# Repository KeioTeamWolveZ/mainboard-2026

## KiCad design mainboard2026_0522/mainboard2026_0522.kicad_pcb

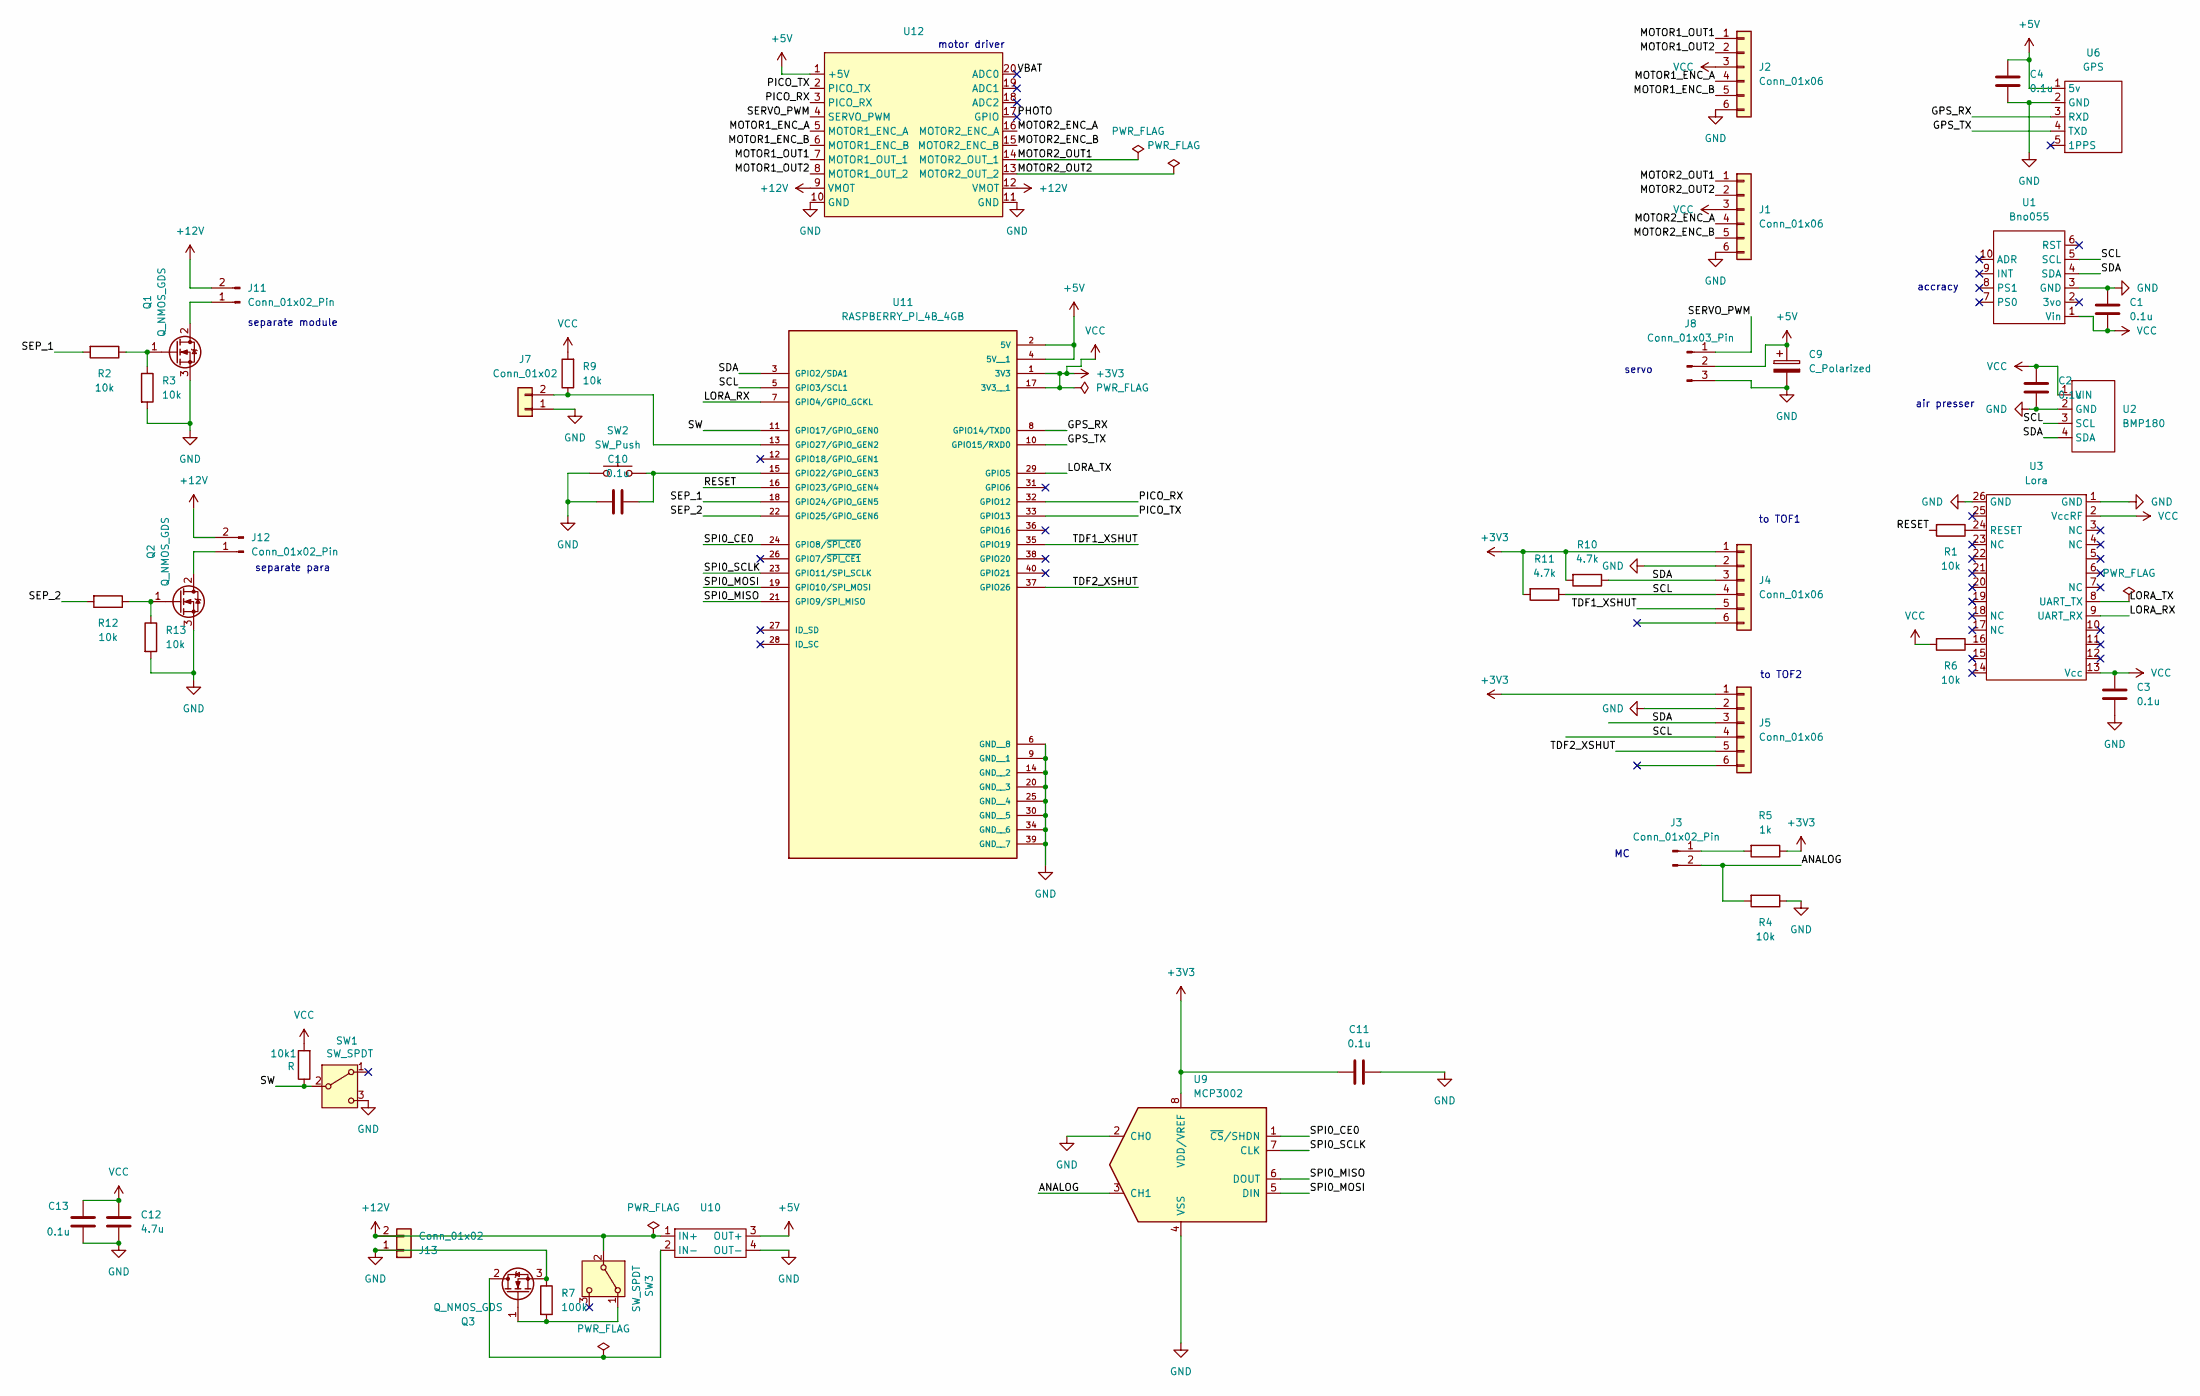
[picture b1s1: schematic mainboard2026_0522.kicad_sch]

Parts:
10k1: R; R_0603_1608Metric_Pad0.98x0.95mm_HandSolder
C1, C2, C3, C4, C10, C11, C13: 0.1u; C_0603_1608Metric_Pad1.08x0.95mm_HandSolder
C9: C_Polarized; CP_Radial_D6.3mm_P2.50mm
C12: 4.7u; C_0603_1608Metric_Pad1.08x0.95mm_HandSolder
J1, J2: Conn_01x06; JST_XH_S6B-XH-A-1_1x06_P2.50mm_Horizontal
J3, J11, J12: Conn_01x02_Pin; JST_PH_B2B-PH-K_1x02_P2.00mm_Vertical
J4, J5: Conn_01x06; JST_ZH_B6B-ZR_1x06_P1.50mm_Horizontal
J7: Conn_01x02; PinHeader_1x02_P2.54mm_Vertical
J8: Conn_01x03_Pin; JST_PH_B3B-PH-K_1x03_P2.00mm_Vertical
J13: Conn_01x02; AMASS_XT30U-M_1x02_P5.0mm_Vertical
Q1, Q2, Q3: Q_NMOS_GDS; TO-252-3_TabPin2
R1, R2, R3, R6, R9, R12, R13: 10k; R_0603_1608Metric_Pad0.98x0.95mm_HandSolder
R4: 10k; R_Axial_DIN0207_L6.3mm_D2.5mm_P10.16mm_Horizontal
R5: 1k; R_Axial_DIN0207_L6.3mm_D2.5mm_P10.16mm_Horizontal
R7: 100k; R_0603_1608Metric_Pad0.98x0.95mm_HandSolder
R10, R11: 4.7k; R_0603_1608Metric_Pad0.98x0.95mm_HandSolder
SW1, SW3: SW_SPDT; SW_Slide-03_Wuerth-WS-SLTV_10x2.5x6.4_P2.54mm
SW2: SW_Push; SW_PUSH_6mm_H7.3mm
U1: Bno055
U2: BMP180; PinHeader_1x04_P2.54mm_Vertical
U3: Lora; LoRa
U6: GPS
U9: MCP3002; DIP-8_W7.62mm
U10: OKL
U11: RASPBERRY_PI_4B_4GB; raspberrypi; PARTREV 4
U12: motor

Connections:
+3V3: 10k1.2, C1.2, C2.1, C3.1, C11.1, C12.2, C13.2, J1.3, J2.3, J4.1, J5.1, R5.1, R6.2, R9.2, R10.2, R11.2, U1.1 (Vin), U2.1 (VIN), U3.2 (VccRF), U3.13 (Vcc), U9.8 (VDD/VREF), U11.1 (3V3), U11.17 (3V3__1)
+5V: C4.1, C9.1, J8.2, U6.1 (5v~), U10.3 (OUT+), U11.2 (5V), U11.4 (5V__1), U12.1 (+5V)
+12V: J11.2, J12.2, J13.2, SW3.2 (B), U10.1 (IN+), U12.9 (VMOT), U12.12 (VMOT)
/ANALOG: J3.2, R4.2, U9.3 (CH1)
/GPS_RX: U6.3 (RXD~), U11.8 (GPIO14/TXD0)
/GPS_TX: U6.4 (TXD~), U11.10 (GPIO15/RXD0)
/LORA_RX: U3.9 (UART_RX), U11.7 (GPIO4/GPIO_GCKL)
/LORA_TX: U3.8 (UART_TX), U11.29 (GPIO5)
/MOTOR1_ENC_A: J2.4, U12.5 (MOTOR1_ENC_A)
/MOTOR1_ENC_B: J2.5, U12.6 (MOTOR1_ENC_B)
/MOTOR1_OUT1: J2.1, U12.7 (MOTOR1_OUT_1)
/MOTOR1_OUT2: J2.2, U12.8 (MOTOR1_OUT_2)
/MOTOR2_ENC_A: J1.4, U12.16 (MOTOR2_ENC_A)
/MOTOR2_ENC_B: J1.5, U12.15 (MOTOR2_ENC_B)
/MOTOR2_OUT1: J1.1, U12.14 (MOTOR2_OUT_1)
/MOTOR2_OUT2: J1.2, U12.13 (MOTOR2_OUT_2)
/PHOTO: U12.17 (GPIO)
/PICO_RX: U11.32 (GPIO12), U12.3 (PICO_RX)
/PICO_TX: U11.33 (GPIO13), U12.2 (PICO_TX)
/RESET: R1.2, U11.16 (GPIO23/GPIO_GEN4)
/SCL: J4.4, J5.4, R11.1, U1.5 (SCL), U2.3 (SCL), U11.5 (GPIO3/SCL1)
/SDA: J4.3, J5.3, R10.1, U1.4 (SDA), U2.4 (SDA), U11.3 (GPIO2/SDA1)
/SEP_1: R2.2, U11.18 (GPIO24/GPIO_GEN5)
/SEP_2: R12.2, U11.22 (GPIO25/GPIO_GEN6)
/SERVO_PWM: J8.1, U12.4 (SERVO_PWM)
/SPI0_CE0: U9.1 (~CS/SHDN), U11.24 (GPIO8/~SPI_CE0)
/SPI0_MISO: U9.6 (DOUT), U11.21 (GPIO9/SPI_MISO)
/SPI0_MOSI: U9.5 (DIN), U11.19 (GPIO10/SPI_MOSI)
/SPI0_SCLK: U9.7 (CLK), U11.23 (GPIO11/SPI_SCLK)
/SW: 10k1.1, SW1.2 (B), U11.11 (GPIO17/GPIO_GEN0)
/TDF1_XSHUT: J4.5, U11.35 (GPIO19)
/TDF2_XSHUT: J5.5, U11.37 (GPIO26)
/VBAT: U12.20 (ADC0)
GND: C1.1, C2.2, C3.2, C4.2, C9.2, C10.1, C11.2, C12.1, C13.1, J1.6, J2.6, J4.2, J5.2, J7.1, J8.3, J13.1, Q1.3 (S), Q2.3 (S), Q3.3 (S), R3.2, R4.1, R7.1, R13.2, SW1.3 (C), SW2.1, U1.3 (GND), U2.2 (GND), U3.1 (GND), U3.26 (GND), U6.2 (GND~), U9.2 (CH0), U9.4 (VSS), U10.4 (OUT-), U11.6 (GND__8), U11.9 (GND__1), U11.14 (GND__2), U11.20 (GND__3), U11.25 (GND__4), U11.30 (GND__5), U11.34 (GND__6), U11.39 (GND__7), U12.10 (GND), U12.11 (GND)
unnamed: J3.1, R5.2
unnamed: J7.2, R9.1, U11.13 (GPIO27/GPIO_GEN2)
unnamed: J11.1, Q1.2 (D)
unnamed: J12.1, Q2.2 (D)
unnamed: Q1.1 (G), R2.1, R3.1
unnamed: Q2.1 (G), R12.1, R13.1
unnamed: Q3.2 (D), U10.2 (IN-)
unnamed: Q3.1 (G), R7.2, SW3.1 (A)
unnamed: R6.1, U3.16
unnamed: R1.1, U3.24 (RESET)
unnamed: C10.2, SW2.2, U11.15 (GPIO22/GPIO_GEN3)

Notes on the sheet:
accracy
air presser
separate para
to TOF1
motor driver
to TOF2
separate module
servo

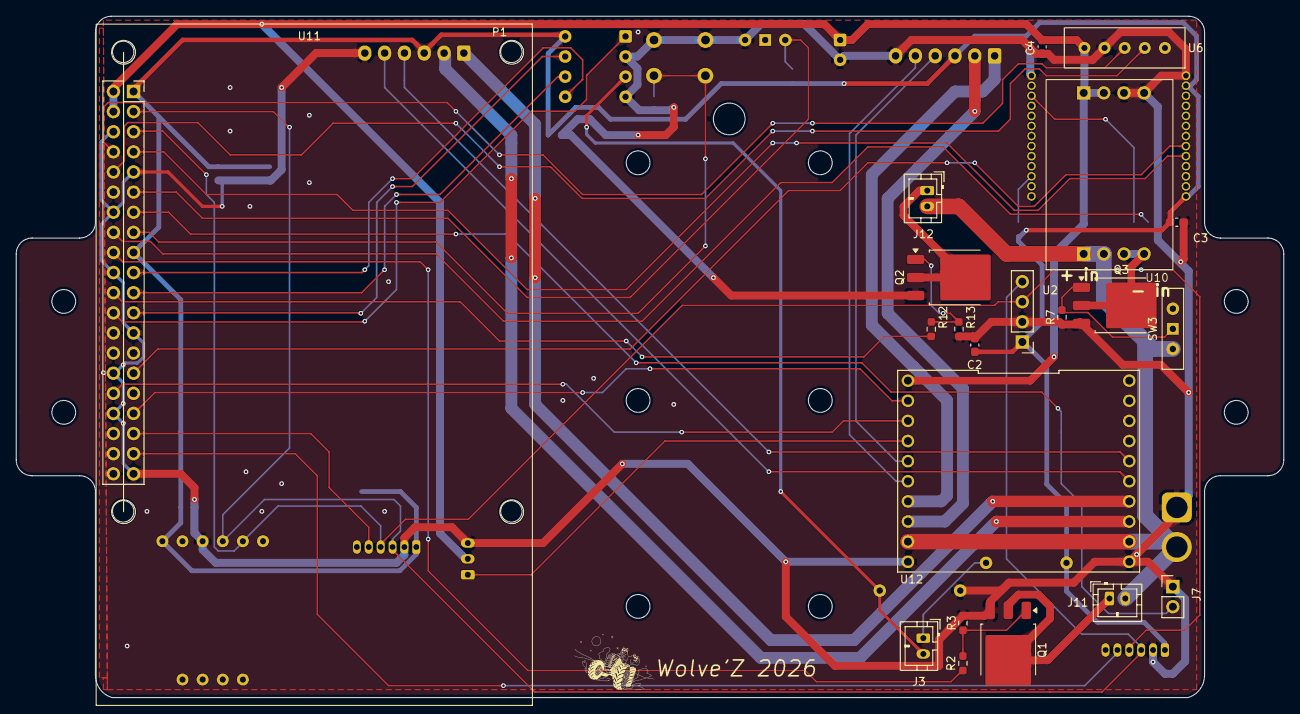
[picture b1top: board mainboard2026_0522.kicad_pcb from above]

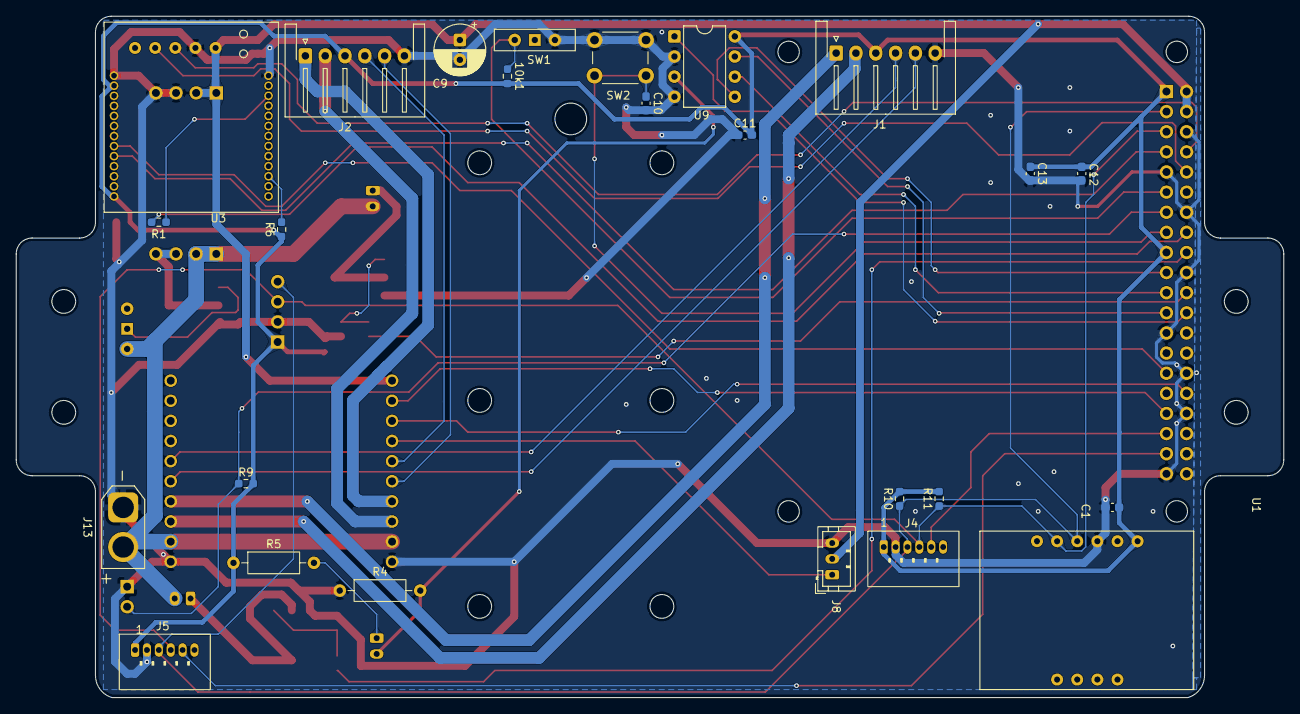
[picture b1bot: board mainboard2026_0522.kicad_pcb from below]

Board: 2 copper layers, 160.0 x 86.0 mm, 46 parts (25 on the bottom side), 43 nets.

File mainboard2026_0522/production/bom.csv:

Designator,Footprint,Quantity,Value,LCSC Part #
10K1,0603,1,R,
"C1, C10, C11, C13, C2, C3, C4",0603,7,0.1u,
C12,0603,1,4.7u,
C9,CP_Radial_D6.3mm_P2.50mm,1,C_Polarized,
"J1, J2",JST_XH_S6B-XH-A-1_1x06_P2.50mm_Horizontal,2,Conn_01x06,
"J11, J12, J3",JST_PH_B2B-PH-K_1x02_P2.00mm_Vertical,3,Conn_01x02_Pin,
J13,AMASS_XT30U-M_1x02_P5.0mm_Vertical,1,Conn_01x02,
"J4, J5",JST_ZH_B6B-ZR_1x06_P1.50mm_Horizontal,2,Conn_01x06,
J7,PinHeader_1x02_P2.54mm_Vertical,1,Conn_01x02,
J8,JST_PH_B3B-PH-K_1x03_P2.00mm_Vertical,1,Conn_01x03_Pin,
"Q1, Q2",TO-252-3_TabPin2,2,Q_NMOS_GDS,
"R1, R12, R13, R2, R3, R4, R6, R9",0603,8,10k,
"R10, R11",0603,2,4.7k,
R5,0603,1,1k,
SW1,SW_Slide-03_Wuerth-WS-SLTV_10x2.5x6.4_P2.54mm,1,SW_SPDT,
SW2,SW_PUSH_6mm_H7.3mm,1,SW_Push,
U1,Bno055,1,Bno055,
U10,OKL,1,~,
U11,raspberrypi,1,RASPBERRY_PI_4B_4GB,
U12,motor,1,~,
U2,PinHeader_1x04_P2.54mm_Vertical,1,BMP180,
U3,LoRa,1,Lora,
U6,GPS,1,GPS,
U9,DIP-8_W7.62mm,1,MCP3002,

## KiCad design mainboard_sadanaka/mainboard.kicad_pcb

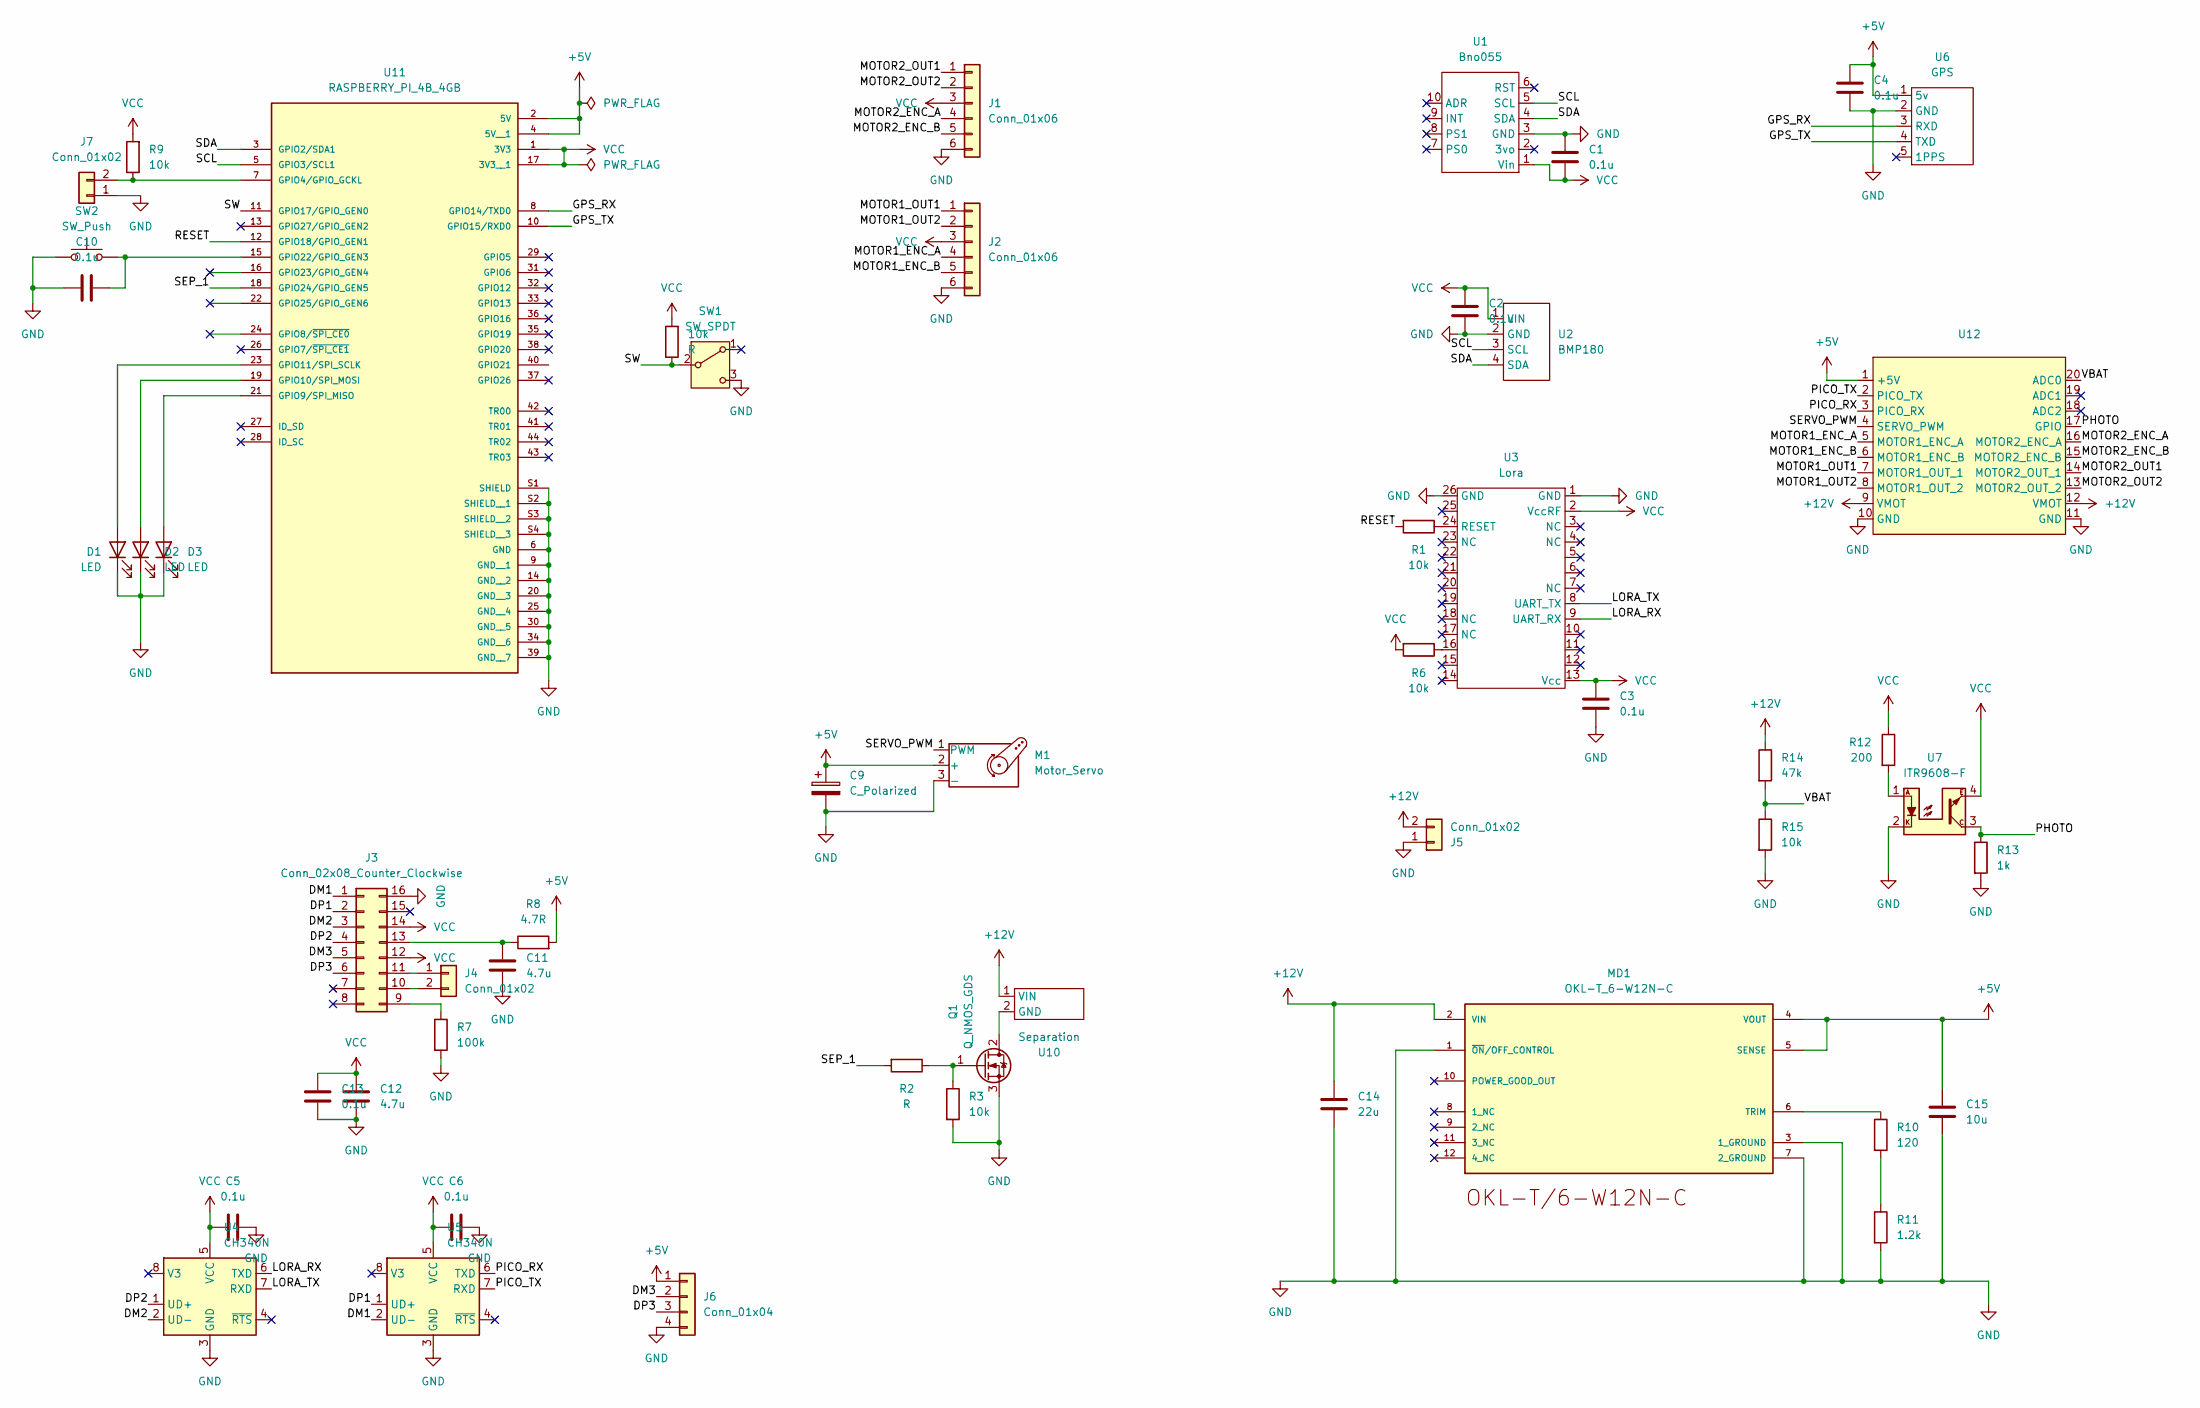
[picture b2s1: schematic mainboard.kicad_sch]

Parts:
10k: R; R_0603_1608Metric_Pad0.98x0.95mm_HandSolder
C1, C2, C3, C4, C5, C6, C10, C13: 0.1u; C_0603_1608Metric_Pad1.08x0.95mm_HandSolder
C9: C_Polarized; CP_Radial_D6.3mm_P2.50mm
C11, C12: 4.7u; C_0603_1608Metric_Pad1.08x0.95mm_HandSolder
C14: 22u; C_0805_2012Metric_Pad1.18x1.45mm_HandSolder
C15: 10u; C_0603_1608Metric_Pad1.08x0.95mm_HandSolder
D1, D2, D3: LED; LED_D3.0mm
J1, J2: Conn_01x06; JST_XH_S6B-XH-A-1_1x06_P2.50mm_Horizontal
J3: Conn_02x08_Counter_Clockwise; SOP-16_4.4x10.4mm_P1.27mm
J4: Conn_01x02; JST_PH_B2B-PH-K_1x02_P2.00mm_Vertical
J5: Conn_01x02; AMASS_XT30U-M_1x02_P5.0mm_Vertical
J6: Conn_01x04; PinHeader_1x04_P2.54mm_Horizontal
J7: Conn_01x02; PinHeader_1x02_P2.54mm_Vertical
M1: Motor_Servo; JST_XH_B3B-XH-A_1x03_P2.50mm_Vertical
MD1: OKL-T_6-W12N-C; MURATA_OKL-T-6-W12N-C_0; MOUSER_PART_NUMBER 580-OKL-T/6-W12N-C; MOUSER_DESCRIPTION Non-Isolated DC/DC Converters 12Vin .59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
Q1: Q_NMOS_GDS; TO-252-3_TabPin2
R1, R3, R6, R9, R15: 10k; R_0603_1608Metric_Pad0.98x0.95mm_HandSolder
R2: R; R_0603_1608Metric_Pad0.98x0.95mm_HandSolder
R7: 100k; R_0603_1608Metric_Pad0.98x0.95mm_HandSolder
R8: 4.7R; R_0603_1608Metric_Pad0.98x0.95mm_HandSolder
R10: 120; R_0603_1608Metric_Pad0.98x0.95mm_HandSolder
R11: 1.2k; R_0603_1608Metric_Pad0.98x0.95mm_HandSolder
R12: 200; R_0603_1608Metric_Pad0.98x0.95mm_HandSolder
R13: 1k; R_0603_1608Metric_Pad0.98x0.95mm_HandSolder
R14: 47k; R_0603_1608Metric_Pad0.98x0.95mm_HandSolder
SW1: SW_SPDT; SW_Slide-03_Wuerth-WS-SLTV_10x2.5x6.4_P2.54mm
SW2: SW_Push; SW_PUSH_6mm_H7.3mm
U1: Bno055
U2: BMP180; PinHeader_1x04_P2.54mm_Vertical
U3: Lora; LoRa
U4, U5: CH340N; SOP-8_3.9x4.9mm_P1.27mm
U6: GPS
U7: ITR9608-F; PinHeader_2x02_P2.54mm_Vertical
U10: Separation; JST_XH_S2B-XH-A_1x02_P2.50mm_Horizontal
U11: RASPBERRY_PI_4B_4GB; Raspberry_Pi_Zero_Socketed_THT_FaceDown_MountingHoles; PARTREV 4
U12: motor

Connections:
+5V: C4.1, C9.1, C15.1, J6.1, M1.2 (+), MD1.4 (VOUT), MD1.5 (SENSE), R8.2, U6.1 (5v~), U11.2 (5V), U11.4 (5V__1), U12.1 (+5V)
+12V: C14.1, J5.2, MD1.2 (VIN), R14.1, U10.1 (VIN), U12.9 (VMOT), U12.12 (VMOT)
/DM1: J3.1, U5.2 (UD-)
/DM2: J3.3, U4.2 (UD-)
/DM3: J3.5, J6.2
/DP1: J3.2, U5.1 (UD+)
/DP2: J3.4, U4.1 (UD+)
/DP3: J3.6, J6.3
/GPS_RX: U6.3 (RXD~), U11.8 (GPIO14/TXD0)
/GPS_TX: U6.4 (TXD~), U11.10 (GPIO15/RXD0)
/LORA_RX: U3.9 (UART_RX), U4.6 (TXD)
/LORA_TX: U3.8 (UART_TX), U4.7 (RXD)
/MOTOR1_ENC_A: J2.4, U12.5 (MOTOR1_ENC_A)
/MOTOR1_ENC_B: J2.5, U12.6 (MOTOR1_ENC_B)
/MOTOR1_OUT1: J2.1, U12.7 (MOTOR1_OUT_1)
/MOTOR1_OUT2: J2.2, U12.8 (MOTOR1_OUT_2)
/MOTOR2_ENC_A: J1.4, U12.16 (MOTOR2_ENC_A)
/MOTOR2_ENC_B: J1.5, U12.15 (MOTOR2_ENC_B)
/MOTOR2_OUT1: J1.1, U12.14 (MOTOR2_OUT_1)
/MOTOR2_OUT2: J1.2, U12.13 (MOTOR2_OUT_2)
/PHOTO: R13.1, U7.3, U12.17 (GPIO)
/PICO_RX: U5.6 (TXD), U12.3 (PICO_RX)
/PICO_TX: U5.7 (RXD), U12.2 (PICO_TX)
/RESET: R1.2, U11.12 (GPIO18/GPIO_GEN1)
/SCL: U1.5 (SCL), U2.3 (SCL), U11.5 (GPIO3/SCL1)
/SDA: U1.4 (SDA), U2.4 (SDA), U11.3 (GPIO2/SDA1)
/SEP_1: R2.2, U11.18 (GPIO24/GPIO_GEN5)
/SERVO_PWM: M1.1 (PWM), U12.4 (SERVO_PWM)
/SW: 10k.1, SW1.2 (B), U11.11 (GPIO17/GPIO_GEN0); also elsewhere on the board
/VBAT: R14.2, R15.1, U12.20 (ADC0)
GND: C1.1, C2.2, C3.2, C4.2, C5.1, C6.1, C9.2, C10.1, C11.1, C12.1, C13.1, C14.2, C15.2, D1.1 (K), D2.1 (K), D3.1 (K), J1.6, J2.6, J3.16, J5.1, J6.4, J7.1, M1.3 (-), MD1.1 (~ON/OFF_CONTROL), MD1.3 (1_GROUND), MD1.7 (2_GROUND), Q1.3 (S), R3.2, R7.2, R11.2, R13.2, R15.2, SW1.3 (C), SW2.1, U1.3 (GND), U2.2 (GND), U3.1 (GND), U3.26 (GND), U4.3 (GND), U5.3 (GND), U6.2 (GND~), U7.2, U11.6 (GND), U11.9 (GND__1), U11.14 (GND__2), U11.20 (GND__3), U11.25 (GND__4), U11.30 (GND__5), U11.34 (GND__6), U11.39 (GND__7), U11.S1 (SHIELD), U11.S2 (SHIELD__1), U11.S3 (SHIELD__2), U11.S4 (SHIELD__3), U12.10 (GND), U12.11 (GND)
unnamed: D1.2 (A), U11.23 (GPIO11/SPI_SCLK)
unnamed: D2.2 (A), U11.19 (GPIO10/SPI_MOSI)
unnamed: D3.2 (A), U11.21 (GPIO9/SPI_MISO)
unnamed: J3.9, R7.1
unnamed: J3.10, J4.2
unnamed: J3.11, J4.1
unnamed: C11.2, J3.13, R8.1
unnamed: J7.2, R9.1, U11.7 (GPIO4/GPIO_GCKL)
unnamed: MD1.6 (TRIM), R10.1
unnamed: Q1.2 (D), U10.2 (GND)
unnamed: Q1.1 (G), R2.1, R3.1
unnamed: R6.1, U3.16
unnamed: R10.2, R11.1
unnamed: R12.2, U7.1
unnamed: R1.1, U3.24 (RESET)
unnamed: C10.2, SW2.2, U11.15 (GPIO22/GPIO_GEN3)
VCC: 10k.2, C1.2, C2.1, C3.1, C5.2, C6.2, C12.2, C13.2, J1.3, J2.3, J3.12, J3.14, R6.2, R9.2, R12.1, U1.1 (Vin), U2.1 (VIN), U3.2 (VccRF), U3.13 (Vcc), U4.5 (VCC), U5.5 (VCC), U7.4, U11.1 (3V3), U11.17 (3V3__1); also elsewhere on the board

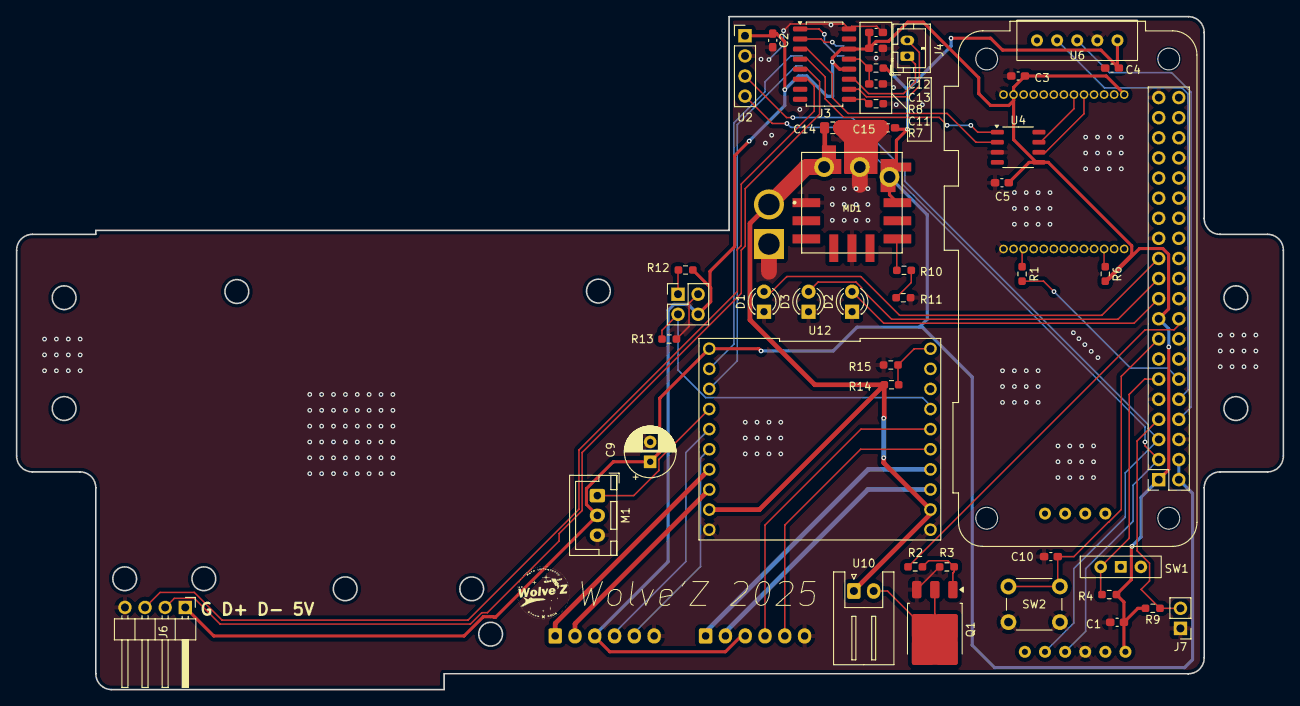
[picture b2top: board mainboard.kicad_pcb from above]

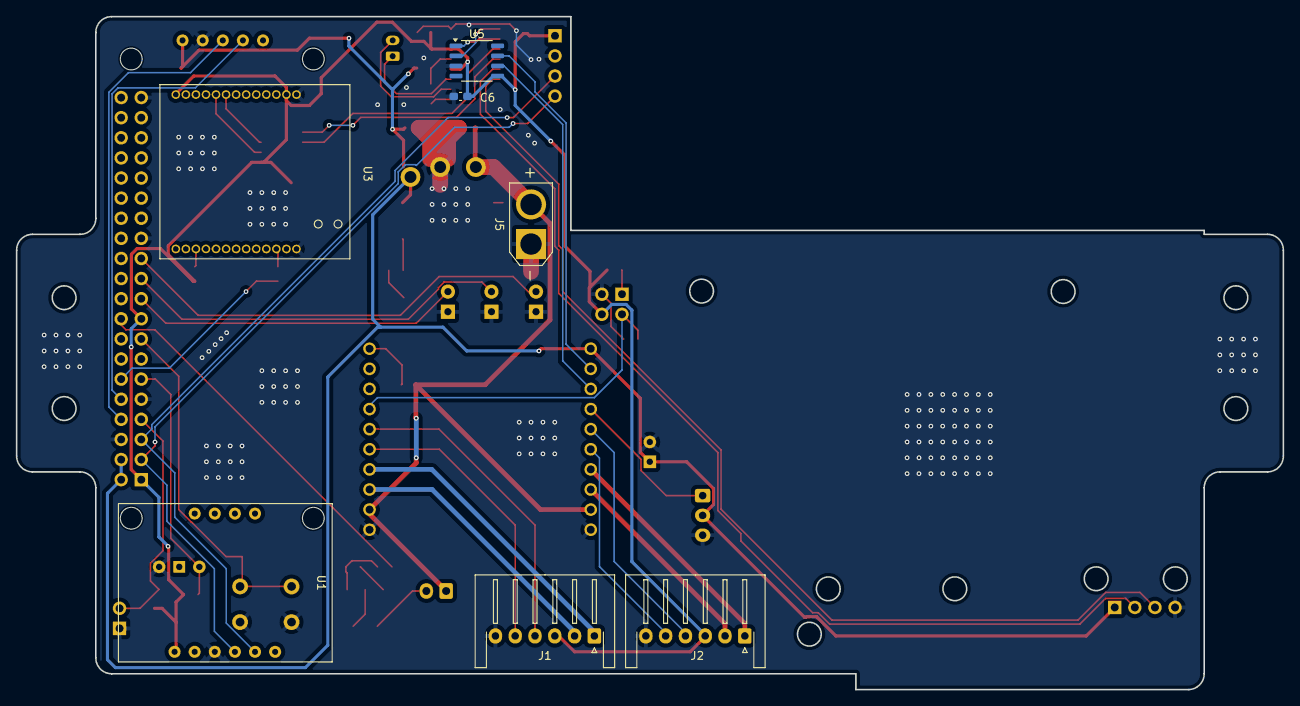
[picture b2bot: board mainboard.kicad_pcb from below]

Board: 2 copper layers, 160.0 x 85.0 mm, 52 parts (7 on the bottom side), 48 nets.

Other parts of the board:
R4: R; R_0603_1608Metric_Pad0.98x0.95mm_HandSolder

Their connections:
/SW: R4.1; also elsewhere on the board
VCC: R4.2; also elsewhere on the board

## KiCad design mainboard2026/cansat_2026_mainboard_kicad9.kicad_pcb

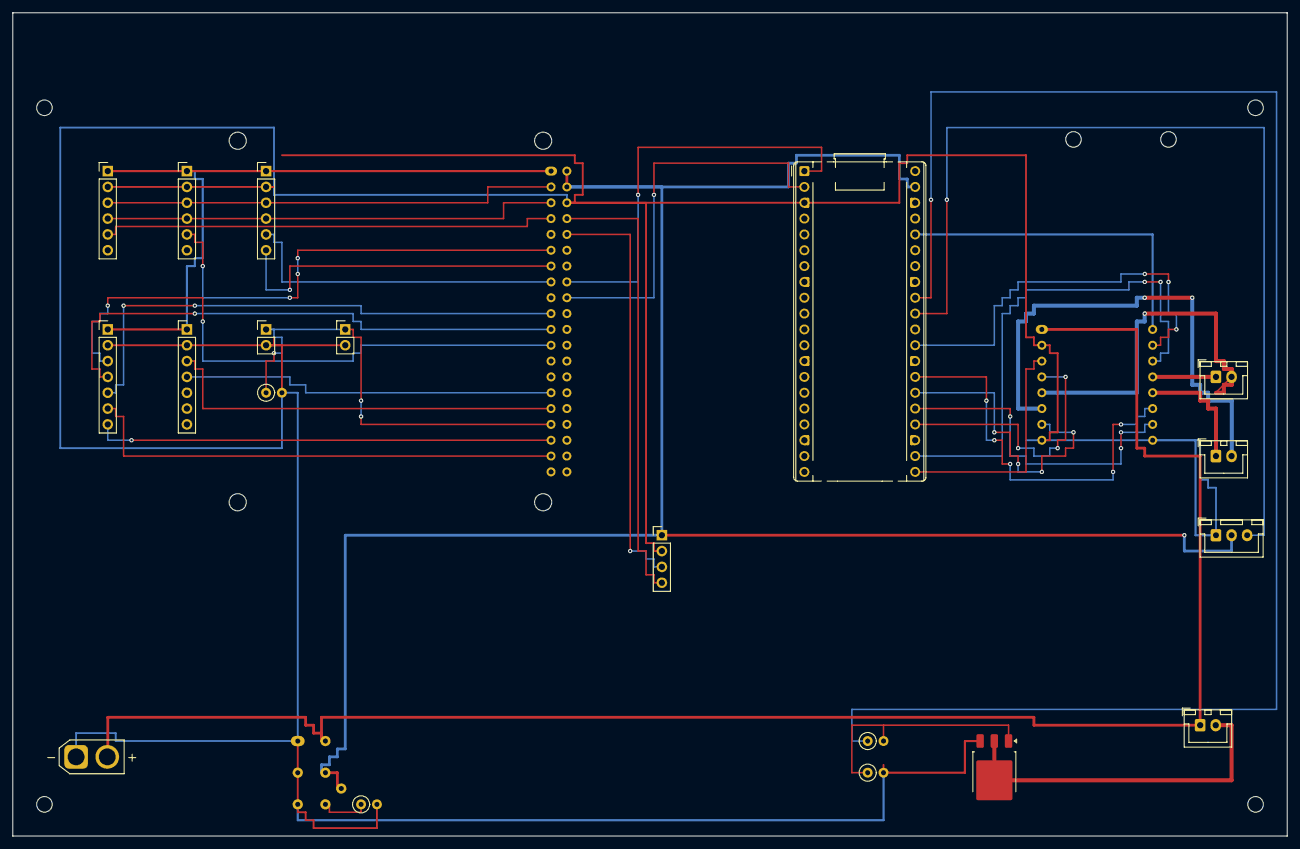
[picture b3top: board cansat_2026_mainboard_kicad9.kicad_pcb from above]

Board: 2 copper layers, 204.5 x 132.1 mm, 28 parts (0 on the bottom side), 39 nets.

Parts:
J_GPS1: u-blox NEO-M8N UART GPS module; PinHeader_1x04_P2.54mm_Vertical
J_IMU1: Adafruit 4754 BNO085 9-DoF IMU; PinHeader_1x06_P2.54mm_Vertical
J_LORA1: Ebyte E220-900T22S LoRa UART; PinHeader_1x07_P2.54mm_Vertical
J_MAG_MOD: 2-pin magnetic connector module; PinHeader_1x02_P2.54mm_Vertical
J_MAG_STAB: 2-pin magnetic connector stabilizer; PinHeader_1x02_P2.54mm_Vertical
J_MOTDRV1: SparkFun ROB-14451 TB6612FNG dual motor driver; SparkFun_TB6612FNG_Carrier_2x08_17.78mm
J_MOTOR_A: JST-XH B2B-XH-A Motor A; JST_XH_B2B-XH-A_1x02_P2.50mm_Vertical
J_MOTOR_B: JST-XH B2B-XH-A Motor B; JST_XH_B2B-XH-A_1x02_P2.50mm_Vertical
J_PWR1: AMASS XT30U-M 12V input; AMASS_XT30U-M_1x02_P5.0mm_Vertical
J_RPI1: Raspberry Pi 4 Model B full-envelope 40-pin inter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; RaspberryPi_4B_40pin_Mount
J_SD1: Adafruit 4682 microSD SPI breakout; PinHeader_1x07_P2.54mm_Vertical
J_SEP1: JST-XH B2B-XH-A separation nichrome; JST_XH_B2B-XH-A_1x02_P2.50mm_Vertical
J_SERVO1: JST-XH B3B-XH-A servo; JST_XH_B3B-XH-A_1x03_P2.50mm_Vertical
J_TOF1: Adafruit 3967 VL53L1X ToF front; PinHeader_1x06_P2.54mm_Vertical
J_TOF2: Adafruit 3967 VL53L1X ToF rear; PinHeader_1x06_P2.54mm_Vertical
MD1: Murata OKL-T/6-W12N-C 12V-to-5V; Murata_OKL-T-6-W12N-C
MH1, MH2, MH3, MH4: M2.5 mounting hole; MountingHole_2.5mm
MH_CAM1, MH_CAM2: Camera cable strain relief M2.5; MountingHole_2.5mm
Q1: IRLR7843PbF NMOS separation low-side; TO-252-3_TabPin2
R_MAG: 10k magnetic detect pulldown; R_Axial_DIN0207_L6.3mm_D2.5mm_P2.54mm_Vertical
R_SEP_G: 100R gate resistor; R_Axial_DIN0207_L6.3mm_D2.5mm_P2.54mm_Vertical
R_SEP_PD: 100k gate pulldown; R_Axial_DIN0207_L6.3mm_D2.5mm_P2.54mm_Vertical
R_TRIM1: DNP OKL trim placeholder; R_Axial_DIN0207_L6.3mm_D2.5mm_P2.54mm_Vertical
U_PICO1: Raspberry Pi Pico H SC0917 motor MCU; RaspberryPi_Pico_Common_THT

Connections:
+3V3: J_IMU1.1, J_LORA1.1, J_RPI1.1, J_SD1.1, J_TOF1.1, J_TOF2.1
+5V: J_GPS1.1, J_RPI1.2, J_RPI1.4, J_SERVO1.2, MD1.4, MD1.5, U_PICO1.39
+12V: J_MOTDRV1.1, J_PWR1.2, J_SEP1.1, MD1.2
BNO_INT: J_IMU1.5, J_RPI1.15
BNO_RST: J_IMU1.6, J_RPI1.13
GND: J_GPS1.2, J_IMU1.2, J_LORA1.2, J_MAG_MOD.2, J_MAG_STAB.2, J_MOTDRV1.3, J_MOTDRV1.15, J_MOTDRV1.16, J_PWR1.1, J_RPI1.6, J_SD1.2, J_SERVO1.1, J_TOF1.2, J_TOF2.2, MD1.1, MD1.3, MD1.7, Q1.3, R_MAG.2, R_SEP_PD.2, R_TRIM1.2, U_PICO1.3
GPS_RX_FROM_PI: J_GPS1.4, J_RPI1.8
GPS_TX_TO_PI: J_GPS1.3, J_RPI1.10
I2C_SCL: J_IMU1.4, J_RPI1.5, J_TOF1.4, J_TOF2.4
I2C_SDA: J_IMU1.3, J_RPI1.3, J_TOF1.3, J_TOF2.3
LORA_RXD_FROM_PI: J_LORA1.4, J_RPI1.29
LORA_TXD_TO_PI: J_LORA1.3, J_RPI1.31
MAG_DETECT: J_MAG_MOD.1, J_MAG_STAB.1, J_RPI1.33, R_MAG.1
MD1_TRIM: MD1.6, R_TRIM1.1
MOTOR_A1: J_MOTDRV1.8, J_MOTOR_A.1
MOTOR_A2: J_MOTDRV1.9, J_MOTOR_A.2
MOTOR_B1: J_MOTDRV1.10, J_MOTOR_B.1
MOTOR_B2: J_MOTDRV1.11, J_MOTOR_B.2
MOT_AIN1: J_MOTDRV1.5, U_PICO1.21
MOT_AIN2: J_MOTDRV1.6, U_PICO1.22
MOT_BIN1: J_MOTDRV1.14, U_PICO1.25
MOT_BIN2: J_MOTDRV1.13, U_PICO1.26
MOT_PWMA: J_MOTDRV1.7, U_PICO1.24
MOT_PWMB: J_MOTDRV1.12, U_PICO1.27
MOT_STBY: J_MOTDRV1.4, U_PICO1.29
PICO_3V3: J_MOTDRV1.2, U_PICO1.36
PICO_TO_PI: J_RPI1.18, U_PICO1.2
PI_TO_PICO: J_RPI1.16, U_PICO1.1
SD_CS: J_RPI1.37, J_SD1.6
SD_DET: J_RPI1.35, J_SD1.7
SD_MISO: J_RPI1.21, J_SD1.4
SD_MOSI: J_RPI1.19, J_SD1.5
SD_SCK: J_RPI1.23, J_SD1.3
SEP_GATE: Q1.1, R_SEP_G.2, R_SEP_PD.1
SEP_GATE_DRV: R_SEP_G.1, U_PICO1.32
SEP_NEG: J_SEP1.2, Q1.2
SERVO_PWM: J_SERVO1.3, U_PICO1.31
TOF1_XSHUT: J_RPI1.7, J_TOF1.5
TOF2_XSHUT: J_RPI1.11, J_TOF2.5

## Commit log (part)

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2026-05-19 20260519
2026-05-19 17:57に更新
2026-05-20 回路図を更新
2026-05-20 20260520
2026-05-21 KiCadプロジェクトを更新
2026-05-22 20260522
2026-05-22 schfinished
2026-05-24 20260524
2026-05-24 2026_0524_19:07
2026-05-27 pcb_precomplete
2026-05-27 fix_pcb
2026-05-28 2026_0528_19:50
2026-05-29 pcb0529
2026-06-01 20260601
2026-06-03 ver1complete
2026-06-03 no changes
2026-06-04 fixpcb
